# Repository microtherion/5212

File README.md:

[KiCad](http://kicad-pcb.org) design of a 5V to 12V booster module, based on the MAX662+ / ST662ABD IC.

PCB available at [OSH Park](https://oshpark.com/projects/VagC95cB)

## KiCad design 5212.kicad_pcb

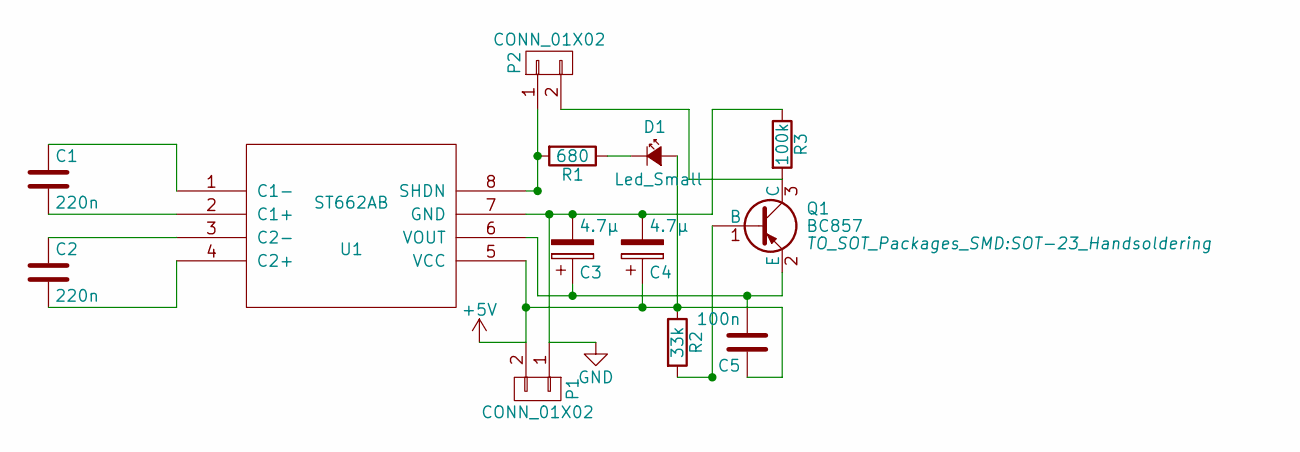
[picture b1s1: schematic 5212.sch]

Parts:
C1, C2: 220n; C_0805_HandSoldering
C3, C4: 4.7µ; SMD-1206_Pol
C5: 100n; C_0603_HandSoldering
D1: Led_Small; SMD-1206_Pol
P1, P2: CONN_01X02; Pin_Header_Straight_1x02
Q1: BC857; SOT-23_Handsoldering
R1: 680; R_0603_HandSoldering
R2: 33k; R_0603_HandSoldering
R3: 100k; R_0603_HandSoldering
U1: ST662AB; SOIC-8-N

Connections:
+5V: C4.1, C5.1, D1.2 (A), P1.2, R2.1, U1.5 (VCC)
GND: C3.2, C4.2, P1.1, R3.1, U1.7 (GND)
unnamed: C1.1, U1.1 (C1-)
unnamed: C1.2, U1.2 (C1+)
unnamed: C2.1, U1.3 (C2-)
unnamed: C2.2, U1.4 (C2+)
unnamed: C3.1, C5.2, Q1.2 (E), U1.6 (VOUT)
unnamed: D1.1 (K), R1.1
unnamed: P2.1, R1.2, U1.8 (SHDN)
unnamed: P2.2, Q1.3 (C), R3.2
unnamed: Q1.1 (B), R2.2

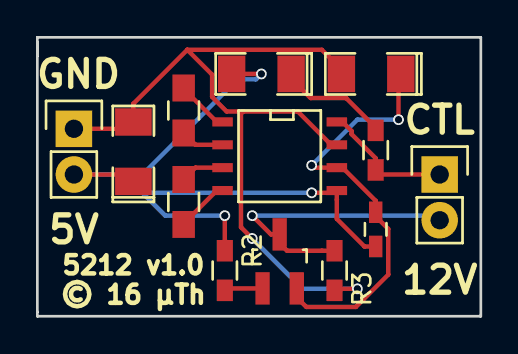
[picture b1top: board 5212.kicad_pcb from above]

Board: 2 copper layers, 24.6 x 15.5 mm, 13 parts (0 on the bottom side), 11 nets.

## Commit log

2016-05-22 5212 v1.0
2016-05-22 Add 3D view
2016-05-22 Add schematic
2016-05-22 Add documentation
2016-06-25 Link to project, not ordering link!

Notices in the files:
5212.kicad_pcb:
© 16 µTh
